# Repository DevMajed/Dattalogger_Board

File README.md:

# MCU Datalogger with memory and clock

## Project Overview: 
**Project Name:**  
MCU Data Logger for ATmega328-AU  
Author: Majed Alharbi [ Majed Dev ]  
URL: https://github.com/DevMajed/Dattalogger_Board.git  

<br>  

<br>  

**Objective :**  
The MCU Data Logger is designed to log data from various sensors or peripherals connected to an ATmega328-AU microcontroller.  
The project incorporates features such as external EEPROM memory (24LC1025), a real-time clock (DS1337S), and essential connectors for communication and programming.

## Block Diagram / Circuit Schematic :

**ATmega328-AU:**  
Main microcontroller responsible for data processing, sensor interfacing, and overall control of the system.

**EEPROM (24LC1025):**  
External EEPROM memory for storing data logs, and it rovides non-volatile extended storage capacity.

**Real-Time Clock (DS1337S):**  
Provides accurate timekeeping for timestamping data logs.

**Real time Crystal Oscillator:**  
32.768 kHz: Connected to DS1337S for precise real-time tracking.

**High speed Crystal Oscillator :**  
16 MHz, Connected to Pins B6 and B7 of the AVR, with capacitors for stable clock operation.

**Connectors:**  
UART: For serial communication.  
ICSP: In-Circuit Serial Programming for firmware updates.  
I2C: General-purpose I2C communication.  
GPIO: General-purpose input/output for additional peripherals.  

**Interactions between Blocks:**  
* The ATmega328-AU communicates with the EEPROM over the I2C bus, storing and retrieving data logs.  
* The DS1337S sends real-time information to the ATmega328-AU, allowing accurate timestamping of data.  
* The 16 MHz crystal oscillator provides the main clock signal for the ATmega328-AU, ensuring proper execution of instructions.  
* Connectors facilitate external communication and programming, enhancing the project's versatility.  

## Specifications:  
Microcontroller: ATmega328-AU  
EEPROM: 24LC1025  
Real-Time Clock: DS1337S  
Crystal Oscillators:  
32.768 kHz (for DS1337S)  
16 MHz (for ATmega328-AU)  
Connectors: UART, ICSP, I2C, GPIO  
Power Supply: 5V battery "MCU 1.8V to 5.5V, EEPROM and DS1337S 2.3V to 5.5V. Oscillators 5V."  
Communication Protocols: I2C, UART  
Programming Language: C/C++  

## PCB Specifications:  
**Sginals Track width :**  
0.25 mm  
**VCC/GND Track width :**   
0.35 mm  
**Signal Layers:**   
Top F.Cu + Ln2.Cu    
**Power Layer  :**  
Ln1.Cu with Copper fills  
**Ground Layer :**  
Bottom B.Cu with Copper fills

## BOM : Bill of materials

# Contact Info
## If you have any questions email me : dev.majed.alharbi@gmail.com

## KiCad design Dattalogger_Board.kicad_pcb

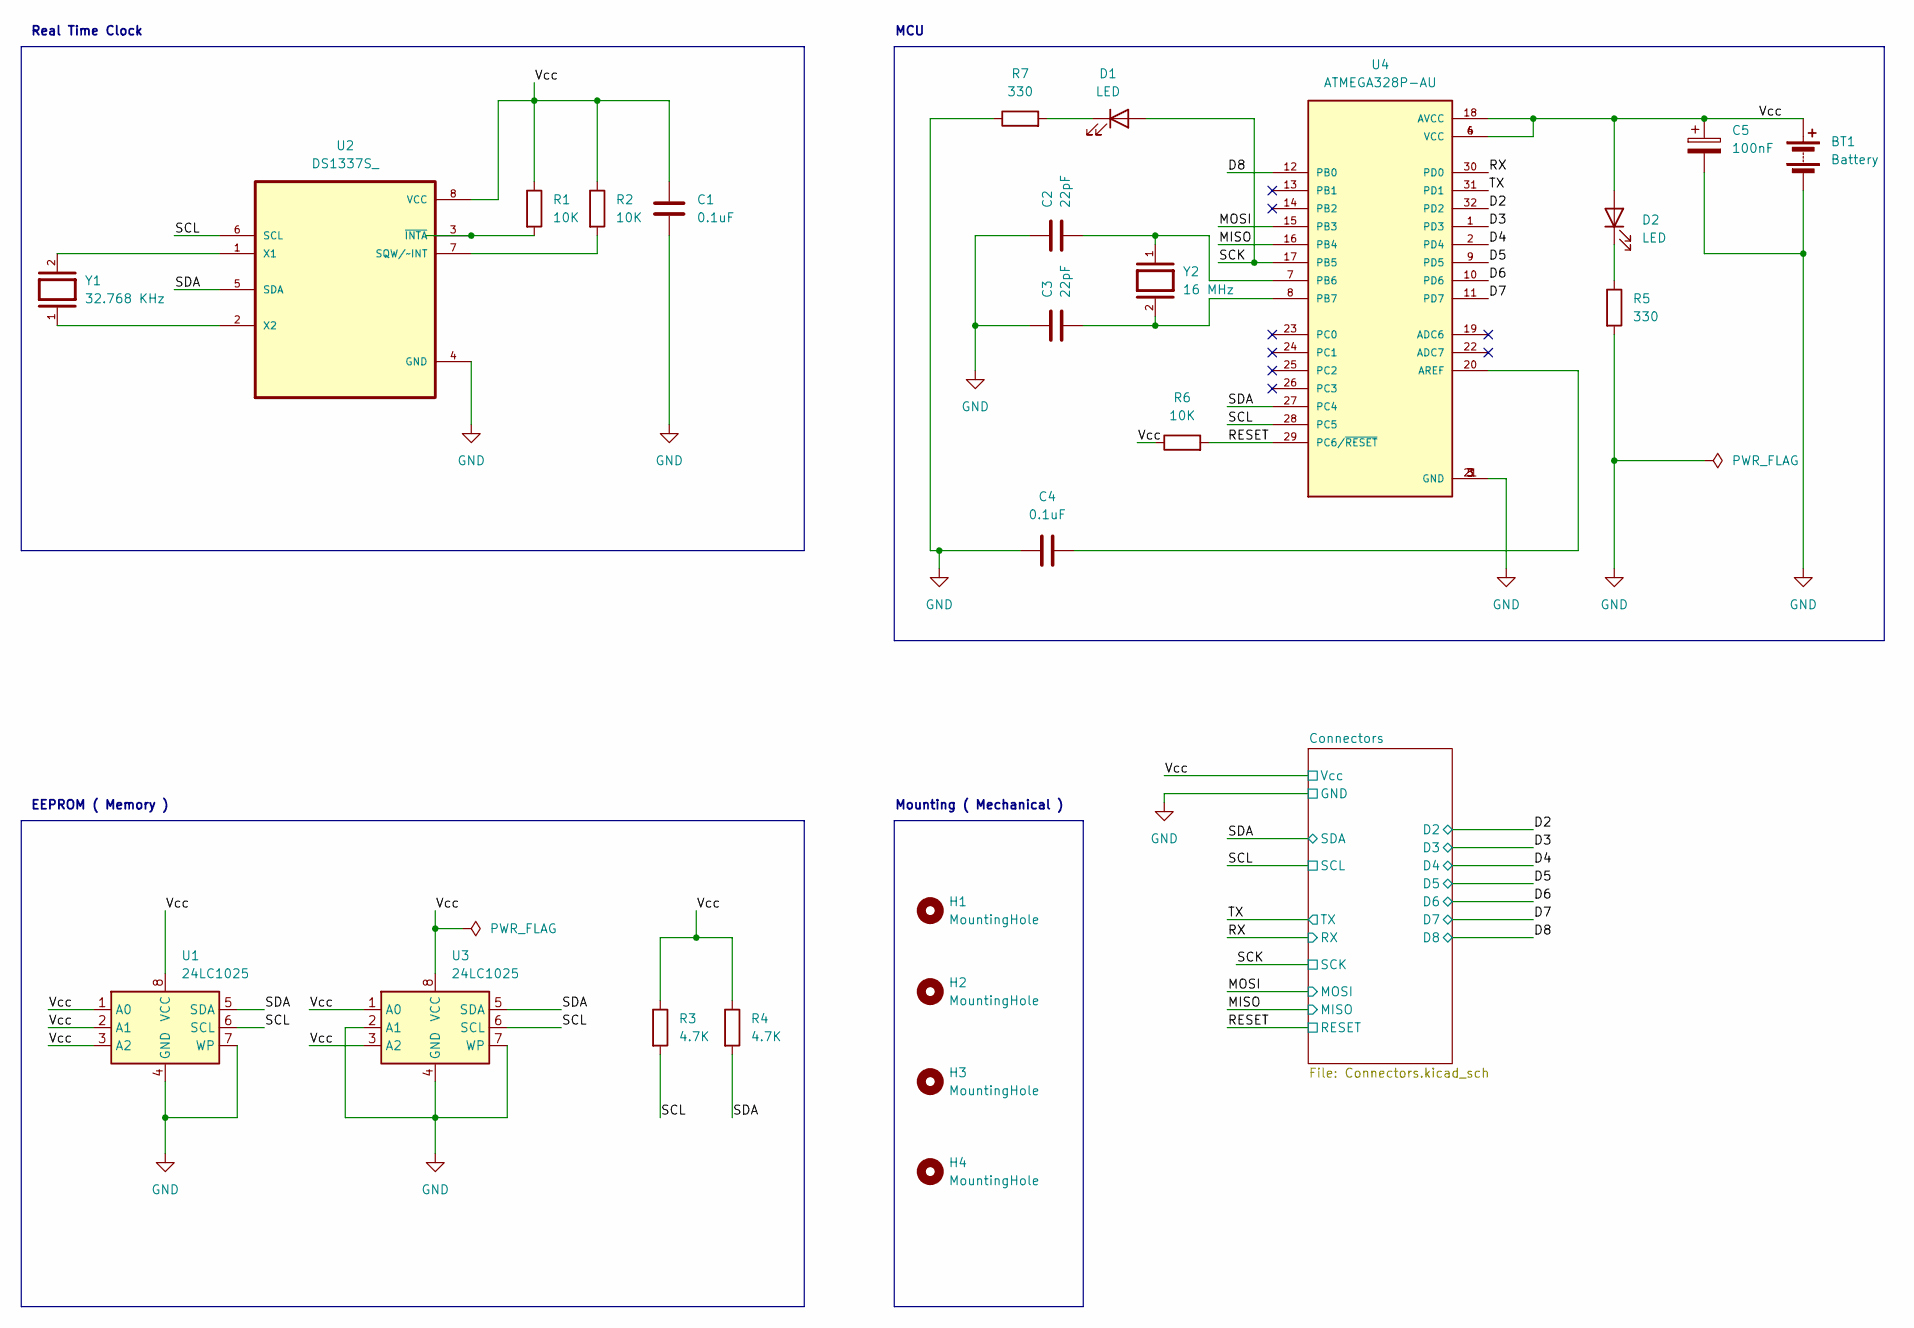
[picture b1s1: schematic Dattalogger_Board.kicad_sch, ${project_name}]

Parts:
BT1: Battery; PinHeader_2x01_P2.54mm_Vertical
C1, C4: 0.1uF; C_0805_2012Metric
C2, C3: 22pF; C_0805_2012Metric
C5: 100nF; C_0805_2012Metric
D1, D2: LED; LED_0805_2012Metric
H1, H2, H3, H4: MountingHole; MountingHole_2.1mm
R1, R2, R6: 10K; R_0805_2012Metric
R3, R4: 4.7K; R_0805_2012Metric
R5, R7: 330; R_0805_2012Metric
U1, U3: 24LC1025; SOIC-8_5.23x5.23mm_P1.27mm
U2: DS1337S_; SOIC127P600X175-8N
U4: ATMEGA328P-AU; QFP80P900X900X120-32N; PARTREV 8271A
Y1: 32.768 KHz; Crystal_SMD_5032-2Pin_5.0x3.2mm_HandSoldering; PARTREV 8.1/03.2021
Y2: 16 MHz; Crystal_SMD_5032-2Pin_5.0x3.2mm_HandSoldering; PARTREV 8.1/03.2021

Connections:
/D2: U4.32 (PD2); also elsewhere on the board
/D3: U4.1 (PD3); also elsewhere on the board
/D4: U4.2 (PD4); also elsewhere on the board
/D5: U4.9 (PD5); also elsewhere on the board
/D6: U4.10 (PD6); also elsewhere on the board
/D7: U4.11 (PD7); also elsewhere on the board
/D8: U4.12 (PB0); also elsewhere on the board
/MISO: U4.16 (PB4); also elsewhere on the board
/MOSI: U4.15 (PB3); also elsewhere on the board
/RESET: R6.2, U4.29 (PC6/~RESET); also elsewhere on the board
/RX: U4.30 (PD0); also elsewhere on the board
/SCK: D1.2 (A), R3.2, U1.6 (SCL), U2.6 (SCL), U3.6 (SCL), U4.17 (PB5), U4.28 (PC5); also elsewhere on the board
/SDA: R4.2, U1.5 (SDA), U2.5 (SDA), U3.5 (SDA), U4.27 (PC4); also elsewhere on the board
/TX: U4.31 (PD1); also elsewhere on the board
/Vcc: BT1.1 (+), C1.1, C5.1, D2.2 (A), R1.1, R2.1, R3.1, R4.1, R6.1, U1.1 (A0), U1.2 (A1), U1.3 (A2), U1.8 (VCC), U2.8 (VCC), U3.1 (A0), U3.3 (A2), U3.8 (VCC), U4.4 (VCC), U4.6 (VCC), U4.18 (AVCC); also elsewhere on the board
GND: BT1.2 (-), C1.2, C2.1, C3.1, C4.1, C5.2, R5.2, R7.1, U1.4 (GND), U1.7 (WP), U2.4 (GND), U3.2 (A1), U3.4 (GND), U3.7 (WP), U4.3 (GND), U4.5 (GND), U4.21 (GND); also elsewhere on the board
unnamed: D1.1 (K), R7.2
unnamed: D2.1 (K), R5.1
unnamed: R2.2, U2.7 (SQW/~INT)
unnamed: U2.1 (X1), Y1.2
unnamed: U2.2 (X2), Y1.1
unnamed: R1.2, U2.3 (~INTA)
unnamed: C4.2, U4.20 (AREF)
unnamed: C2.2, U4.7 (PB6), Y2.1
unnamed: C3.2, U4.8 (PB7), Y2.2

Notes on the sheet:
MCU
EEPROM ( Memory )
Mounting ( Mechanical )
Real Time Clock

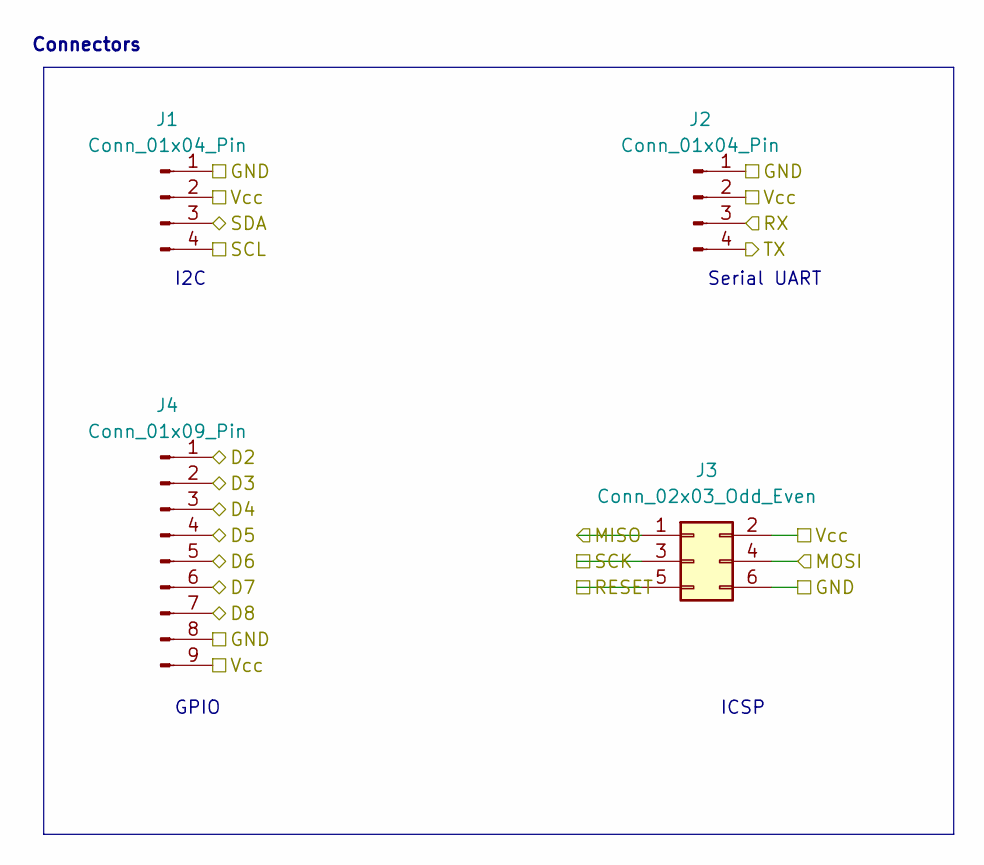
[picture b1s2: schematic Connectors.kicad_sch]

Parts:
J1, J2: Conn_01x04_Pin; PinHeader_1x04_P2.54mm_Vertical
J3: Conn_02x03_Odd_Even; PinHeader_2x03_P2.54mm_Vertical
J4: Conn_01x09_Pin; PinHeader_1x09_P2.54mm_Vertical

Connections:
/D2: J4.1; also elsewhere on the board
/D3: J4.2; also elsewhere on the board
/D4: J4.3; also elsewhere on the board
/D5: J4.4; also elsewhere on the board
/D6: J4.5; also elsewhere on the board
/D7: J4.6; also elsewhere on the board
/D8: J4.7; also elsewhere on the board
/MISO: J3.1; also elsewhere on the board
/MOSI: J3.4; also elsewhere on the board
/RESET: J3.5; also elsewhere on the board
/RX: J2.3; also elsewhere on the board
/SCK: J1.4, J3.3; also elsewhere on the board
/SDA: J1.3; also elsewhere on the board
/TX: J2.4; also elsewhere on the board
/Vcc: J1.2, J2.2, J3.2, J4.9; also elsewhere on the board
GND: J1.1, J2.1, J3.6, J4.8; also elsewhere on the board

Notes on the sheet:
Connectors
ICSP
GPIO
Serial UART
I2C

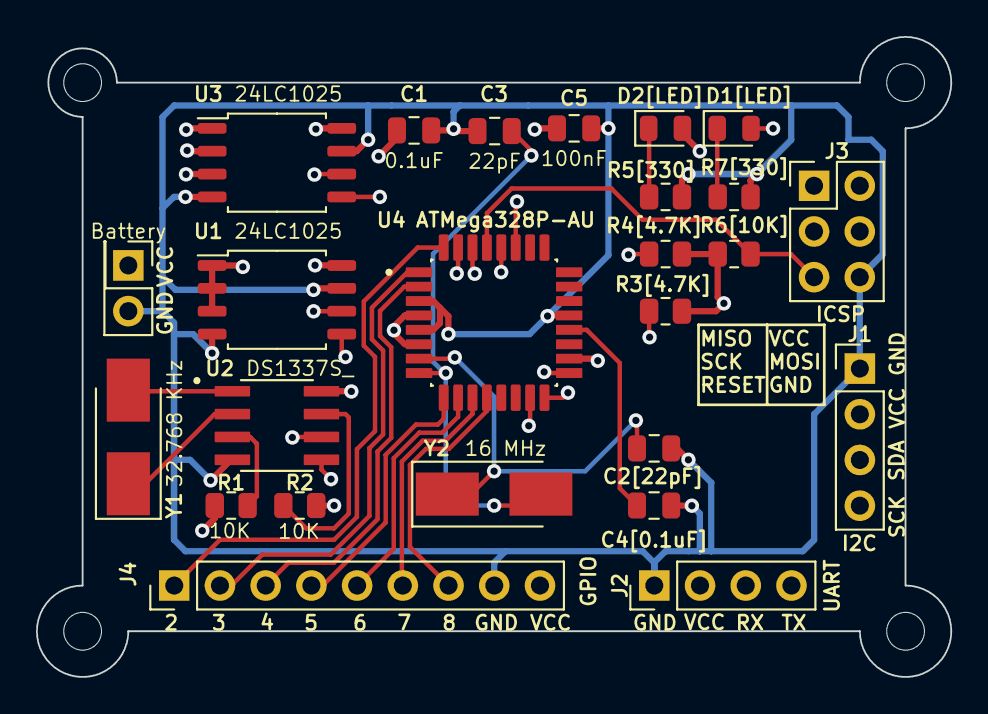
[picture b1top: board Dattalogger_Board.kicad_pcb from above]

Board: 4 copper layers, 50.8 x 35.6 mm, 30 parts (1 on the bottom side), 25 nets.

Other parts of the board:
Majed: LOGO; MajedDev

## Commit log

2024-01-16 First commit of new project.
2024-01-16 preparing new project
2024-01-17 Have added required symbols to the schematic sheets.
2024-01-17 Changed Locations of Symbols (arrange).
2024-01-17 Added Components Values
2024-01-17 Completed Symbol-Footprint associations.
2024-01-17 More footprint assignment
2024-01-17 The wiring for the root sheet is complete.
2024-01-17 Allocated GND and Vcc Nets to the power net class
2024-01-17 Addoed Power Flag and finished ERC
2024-01-17 Completed comments
2024-01-17 Orgnizing schematic and making new branch
2024-01-17 finishing schematic
2024-01-17 Setting up layout Pcbnew
2024-01-17 Completed Placments of footprints and sizing the board
2024-01-17 Completed footprint placments and board sizing
2024-01-17 Refined and completed outline
2024-01-18 Completed Routing
2024-01-18 Completed the 2-layer board
2024-01-19 Completed 2-Layer PCB
2024-01-19 Committing local changes before merge
2024-01-19 Completed 2 Layer PCB
2024-01-19 Completed the 2 Layer PCB
2024-01-19 Completed 3-layer pcb routing
2024-01-19 fixed two defects in the schematic.
2024-01-19 fixed bugs in schematic
2024-01-19 Fixing Bugs & merging projects in one folder
2024-01-19 Completed
